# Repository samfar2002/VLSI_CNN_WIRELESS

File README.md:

# VLSI_CNN_WIRELESS

This GitHub Repository includes all of the necessary files for wireless communications for the CNN ASIC chip designed by the Northwestern VLSI Laboratory.

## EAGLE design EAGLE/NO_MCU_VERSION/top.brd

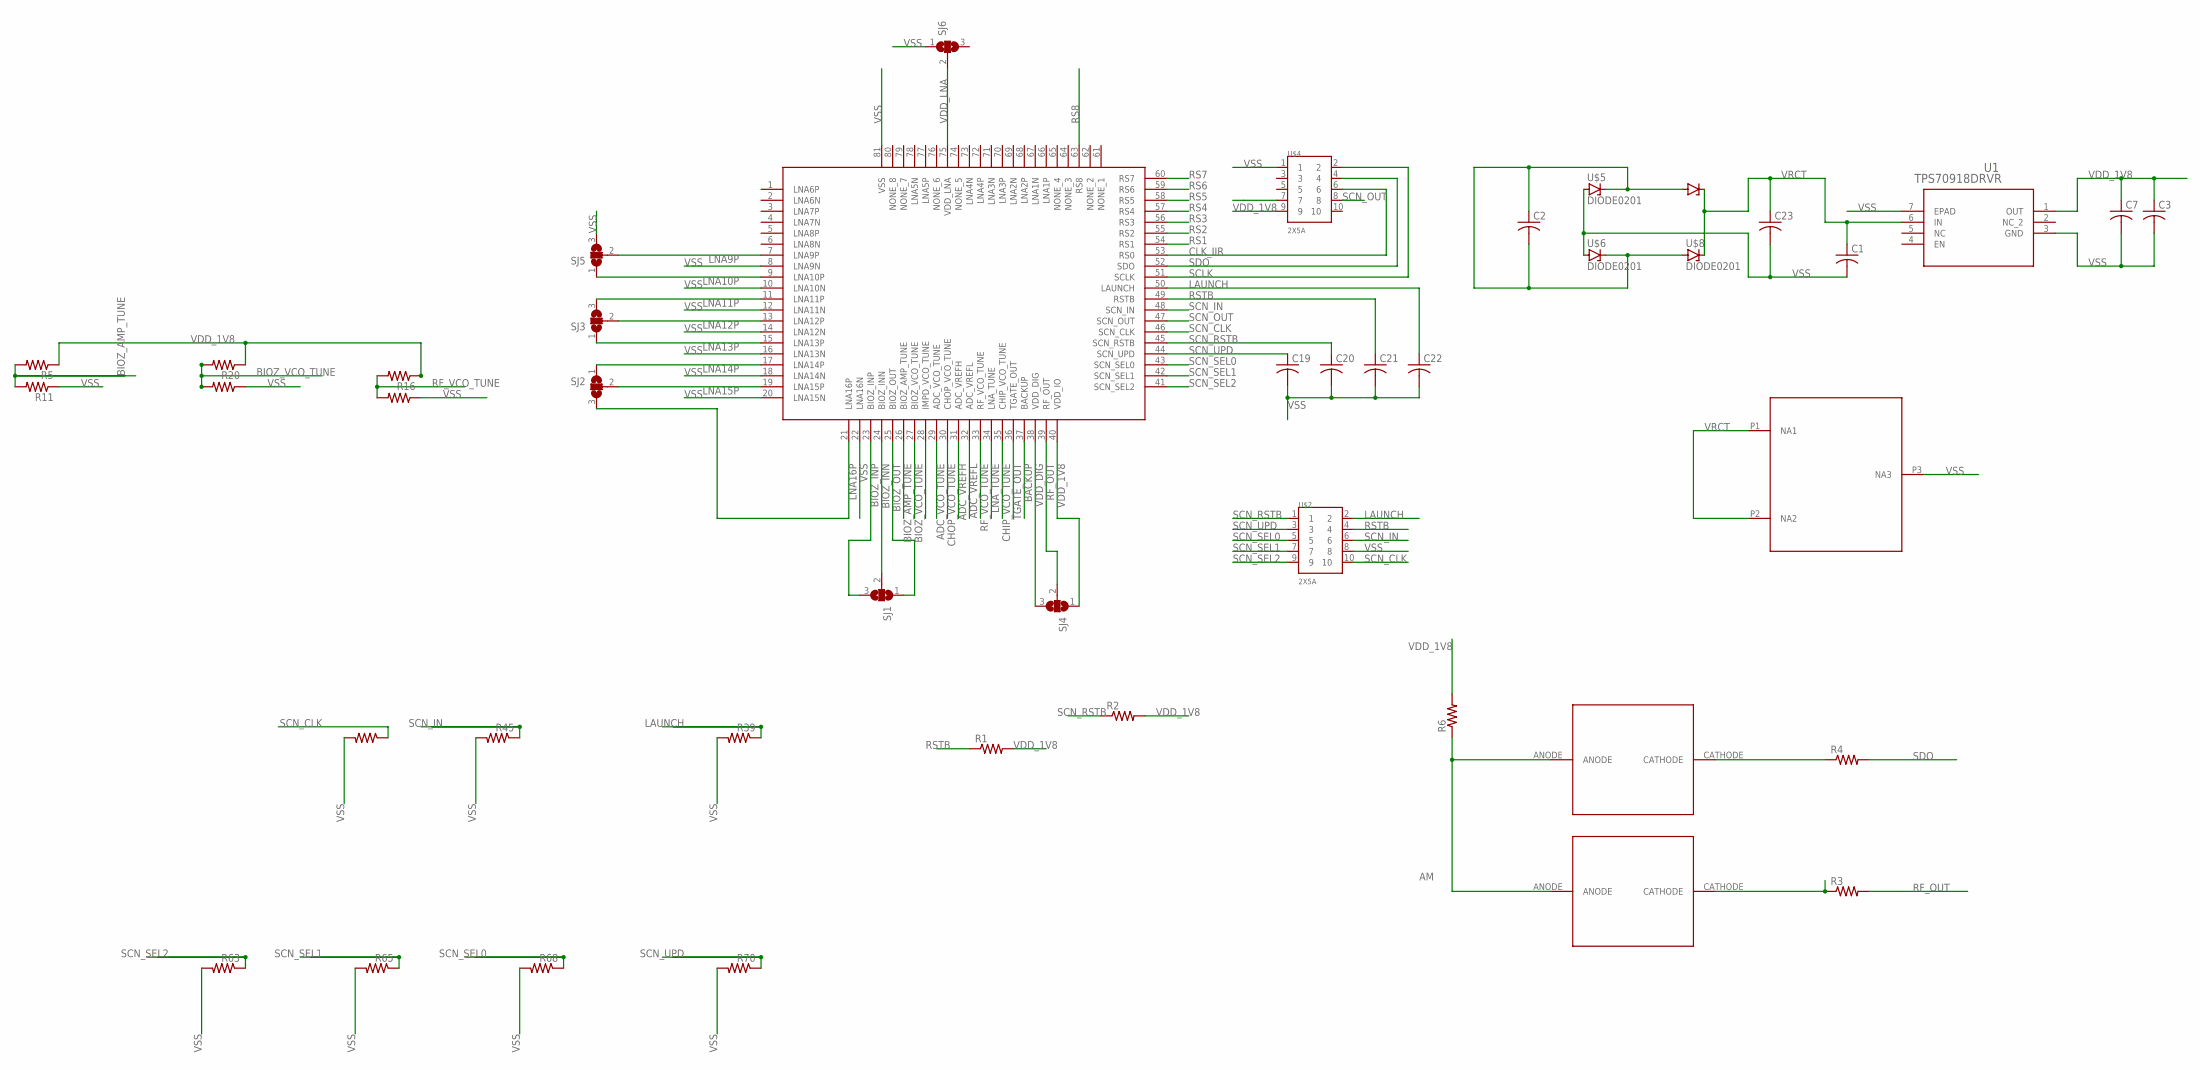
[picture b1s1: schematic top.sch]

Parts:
C1, C3: C-USC0402; C0402
C2, C19, C20, C21, C22: C-USC0201; C0201
C7, C23: C-USC1210; C1210
R1, R2, R3, R4, R6, R39, R45, R47, R63, R65, R68, R70: R-US_R0402; R0402
R5, R11, R16, R17, R20, R22: R-US_R0201; R0201
SJ1, SJ2, SJ3, SJ4, SJ5, SJ6: SJ2W; SJ_2
U1: TPS70918DRVR; DRV6_1P6X1_TEX
U$1: CHIP_QFN; QFN50P1200X1200X80-81T900N
U$2, U$4: 2X5A; 2X5-FCI_UNSHROUDED
U$3: 3030TR
U$5, U$6, U$7, U$8: DIODE0201; C0201
U$9, U$10: MSWSE-050-17; DIODE_MSWSE-050-17

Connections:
ADC_VCO_TUNE: U$1.29 (ADC_VCO_TUNE)
ADC_VREFH: U$1.31 (ADC_VREFH)
ADC_VREFL: U$1.32 (ADC_VREFL)
AM: R6.1, U$4.7, U$9.ANODE, U$10.ANODE
BACKUP: U$1.37 (BACKUP)
BIOZ_AMP_TUNE: R5.2, R11.2, U$1.26 (BIOZ_AMP_TUNE)
BIOZ_INN: SJ1.2, U$1.24 (BIOZ_INN)
BIOZ_INP: SJ1.3, U$1.23 (BIOZ_INP)
BIOZ_OUT: SJ1.1, U$1.25 (BIOZ_OUT)
BIOZ_VCO_TUNE: R20.2, R22.2, U$1.27 (BIOZ_VCO_TUNE)
CHIP_VCO_TUNE: U$1.35 (CHIP_VCO_TUNE)
CHOP_VCO_TUNE: U$1.30 (CHOP_VCO_TUNE)
CLK_IIR: U$1.53 (RS0), U$4.6
LAUNCH: C22.1, R39.1, U$1.50 (LAUNCH), U$2.2
LNA9P: SJ5.2, U$1.7 (LNA9P)
LNA10P: SJ5.1, U$1.9 (LNA10P)
LNA11P: SJ3.3, U$1.11 (LNA11P)
LNA12P: SJ3.2, U$1.13 (LNA12P)
LNA13P: SJ3.1, U$1.15 (LNA13P)
LNA14P: SJ2.1, U$1.17 (LNA14P)
LNA15P: SJ2.2, U$1.19 (LNA15P)
LNA16P: SJ2.3, U$1.21 (LNA16P)
LNA_TUNE: U$1.34 (LNA_TUNE)
unnamed: R4.1, U$9.CATHODE
unnamed: R3.1, U$10.CATHODE
unnamed: C2.1, C2.2, U$5.2 (C), U$6.2 (C), U$7.1 (A), U$8.1 (A)
RF_OUT: R3.2, SJ4.2, U$1.39 (RF_OUT)
RF_VCO_TUNE: R16.2, R17.2, U$1.33 (RF_VCO_TUNE)
RS1: U$1.54 (RS1)
RS2: U$1.55 (RS2)
RS3: U$1.56 (RS3)
RS4: U$1.57 (RS4)
RS5: U$1.58 (RS5)
RS6: U$1.59 (RS6)
RS7: U$1.60 (RS7)
RS8: U$1.63 (RS8)
RSTB: C21.1, R1.1, U$1.49 (RSTB), U$2.4
SCLK: U$1.51 (SCLK), U$4.2
SCN_CLK: R47.1, U$1.46 (SCN_CLK), U$2.10
SCN_IN: R45.1, U$1.48 (SCN_IN), U$2.6
SCN_OUT: U$1.47 (SCN_OUT), U$4.8
SCN_RSTB: C20.1, R2.1, U$1.45 (SCN_RSTB), U$2.1
SCN_SEL0: R68.1, U$1.43 (SCN_SEL0), U$2.5
SCN_SEL1: R65.1, U$1.42 (SCN_SEL1), U$2.7
SCN_SEL2: R63.1, U$1.41 (SCN_SEL2), U$2.9
SCN_UPD: C19.1, R70.1, U$1.44 (SCN_UPD), U$2.3
SDO: R4.2, U$1.52 (SDO), U$4.4
TGATE_OUT: U$1.36 (TGATE_OUT)
VDD_1V8: C3.1, C7.1, R1.2, R2.2, R5.1, R6.2, R16.1, R20.1, SJ4.1, U1.1 (OUT), U$1.40 (VDD_IO), U$4.9
VDD_DIG: SJ4.3, U$1.38 (VDD_DIG)
VDD_LNA: SJ6.2, U$1.75 (VDD_LNA)
VRCT: C1.1, C23.1, U1.6 (IN), U$3.P1 (NA1), U$3.P2 (NA2), U$7.2 (C), U$8.2 (C)
VSS: C1.2, C3.2, C7.2, C19.2, C20.2, C21.2, C22.2, C23.2, R11.1, R17.1, R22.1, R39.2, R45.2, R47.2, R63.2, R65.2, R68.2, R70.2, SJ5.3, SJ6.1, U1.3 (GND), U1.7 (EPAD), U$1.8 (LNA9N), U$1.10 (LNA10N), U$1.12 (LNA11N), U$1.14 (LNA12N), U$1.16 (LNA13N), U$1.18 (LNA14N), U$1.20 (LNA15N), U$1.22 (LNA16N), U$1.81 (VSS), U$2.8, U$3.P3 (NA3), U$4.1, U$5.1 (A), U$6.1 (A)

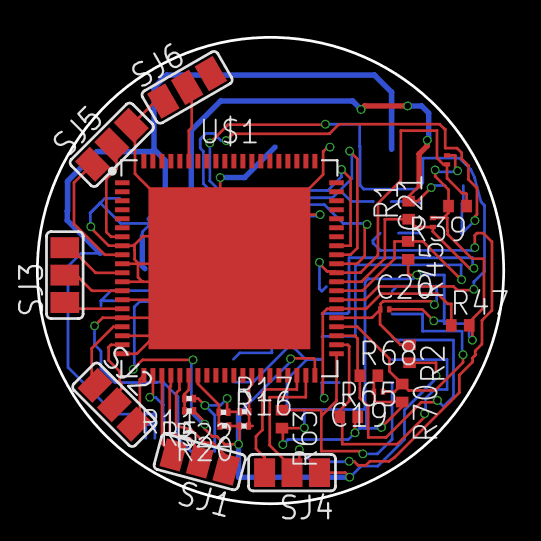
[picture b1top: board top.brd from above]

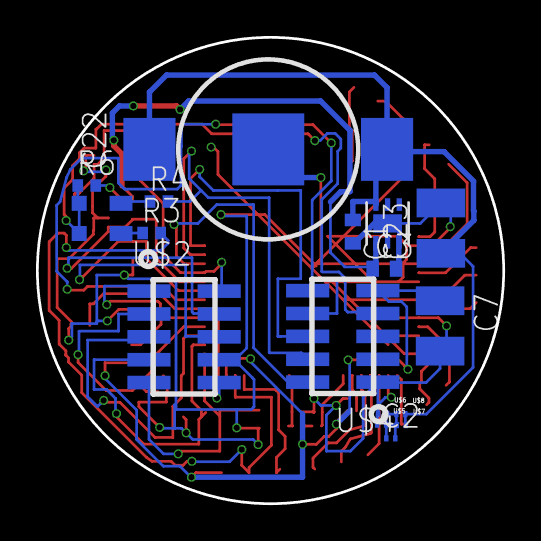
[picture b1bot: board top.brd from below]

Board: 2 copper layers, 25.9 x 25.9 mm, 44 parts (18 on the bottom side), 37 nets.

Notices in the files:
parts and their libraries:
VLSI_qfn56: COPYRIGHT: Copyright (C) 2023 Ultra Librarian. All rights reserved.
SparkFun-Connectors: Licensing: Creative Commons ShareAlike 4.0 International - https://creativecommons.org/licenses/by-sa/4.0
